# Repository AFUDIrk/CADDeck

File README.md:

# CADdeck

The english [Manual](/READMEeng.md) 

Hierbei handelt es sich um ein kombiniertes Joystick- und Touchpanel-Display, das für die Verwendung mit gängigen CAD-Programmen geeignet ist. Es beinhaltet:
1. Zwei-Achsen-Joystick (z. B. für X-, Y-Schwenk)
2. Hall-Sensoren im Joystick-Griff (z. B. für Zoom und Drehung) mit einem berührungslosen Sensor (z. B. zum Bewegen der Komponente in Kombination mit dem Joystick)
3. Zehn Schalter rund um die Basis (z. B. Messen, ESC...)
4. LCD-Touchpanel mit bis zu 10 Bildschirmen und 12 Tasten

Alle H/W-Tasten und die Touchpanel-Tasten sind über eine Website programmierbar.

Die Verbindung zum PC erfolgt per Bluetooth über die HID-Schnittstelle (d. h. für den PC sieht es aus wie eine Tastatur und eine Maus).
Für die Stromversorgung und das Herunterladen von Code steht ein USB-C-Anschluss zur Verfügung.
Der USB-C-Anschluss auf der Rückseite dient der Stromversorgung zum Hochladen des Codes.
Es sollte möglich sein, das Gerät mit Strom zu versorgen und es fest mit dem Bildschirm zu verbinden, anstatt es über USB-C mit Strom zu versorgen, aber das habe ich noch nicht versucht.

Es wurde von Andrew eine USB-Schnitstelle mit einem RP2040 hinzugefügt, mit der das CADDeck 6DOF fähig ist. Es wird noch daran gearbeitet, den Code so zu ändern,
das nur noch ein Prozessor gebraucht wird. Momentan ist noch eine Bluetooth- und eine USB-Verbindung nötig, damit das ganze funktioniert.

Die Firmware für den RP2040 ist von https://github.com/jfedor2/magellan-spacemouse.
Die Version für das CADDeck ist hier zu finden: https://github.com/AFUDIrk/magellan-spacemouse

## Touch-Panel
Das Touchpanel ist von Dustin Watts FreeTouchDeck-Projekt (https://github.com/DustinWatts/FreeTouchDeck.git) inspiriert, das ich modifiziert habe, um die Anzahl der Tasten zu erhöhen.
usw. (https://github.com/andrewfernie/FreeTouchDeckWT32.git). Für dieses Projekt habe ich Joystick-, Hallsensor- und Tastenunterstützung hinzugefügt.
Der einfachste Weg, dies in Gang zu bringen, ist die Verwendung einer WT32-SC01-Karte (http://www.wireless-tag.com/portfolio/wt32-sc01/).
Kaufen Sie das Basisboard, nicht die „Plus“-Version, da das Plus eine parallele Schnittstelle zum LCD-Panel nutzt und nicht genügend IO-Leitungen für den Joystick und die Tasten frei lässt.
usw. Das Board enthält ein ESP32-Modul und ein 3,5-Zoll-LCD mit kapazitivem Touchscreen.

## S/W-Aufbau-Hinweise:
1. Der Build verwendet die PlatformIO-IDE für VSCode. Installieren Sie VSCode, dann das PlatformIO-Plugin und schon kann es losgehen.
2. Sie müssen sicherstellen, dass die entsprechenden Pins für Ihre Hardwarekonfiguration definiert sind. Ich habe meines für den WT32-SC01 gebaut und den Code für ein handverdrahtetes ESP32-Modul + einen resistiven Touchscreen erstellt.
3. Möglicherweise sehen Sie Build-Meldungen wie
 
In der Datei, die aus include/CADDeck.h:14 enthalten ist,
aus include/SaveConfig.h:3,
von src/SaveConfig.cpp:1:
.pio/libdeps/esp-wrover-kit/TFT_eSPI/TFT_eSPI.h:909:8: Warnung: #warning >>>>------>> TOUCH_CS-Pin nicht definiert, TFT_eSPI-Touchfunktionen sind nicht zugänglich! [-Wcpp]
#Warnung >>>>------>> TOUCH_CS-Pin nicht definiert, TFT_eSPI-Touchfunktionen sind nicht verfügbar!`
 
Sie können diese beseitigen, indem Sie TOUCH_CS in platformio.ini für jeden nicht verwendeten Pin definieren, der ein gültiger Ausgabepin ist.
Die Alternative besteht darin, TOUCH_CS nicht zu definieren (die Zeile löschen oder ein Semikolon davor einfügen) und die Meldungen einfach zu ignorieren.

#define TOUCH_CS=33

4. Das System versucht beim Start, das Logo in CADDeck_logo.bmp anzuzeigen. Wenn Sie nicht möchten, dass etwas angezeigt wird, stellen Sie sicher, dass die Datei nicht existiert. In diesem Fall wird auf der seriellen Schnittstelle eine Meldung wie die folgende angezeigt.
Solange Sie beim Start nichts gesehen haben, ignorieren Sie die Meldung.
 
[ 1159][E][vfs_api.cpp:104] open(): /littlefs/logos/CADDeck_logo.bmp existiert nicht, keine Berechtigungen zum Erstellen

5. Möglicherweise werden Ihnen Fehlermeldungen wie z. B. angezeigt
 
[vfs_api.cpp:104] open(): /littlefs/list existiert nicht
 
Dies ist ein bekanntes Problem mit ESPAsyncWebsServer im Zusammenhang mit von LittleFS unterstützten Ordnern, während dies bei SPIFFS nicht der Fall ist. Siehe https://github.com/lorol/

6. Haben Sie Probleme? Es gibt einige Debug-Meldungen, die in FreeTouchDeck.h aktiviert werden können
 
#define LOG_MSG_BASIC 1
#define LOG_MSG_LEVEL 1 // 1=FEHLER, 2=FEHLER+WARN, 3=FEHLER+WARN+INFO
#define LOG_MSG_DEBUG 0
#define LOG_MSG_TOUCH_DEBUG 0 // Meldungen an die Konsole jedes Mal, wenn eine Berührung erkannt wird

Versuchen Sie, LOG_MSG_LEVEL auf 3 zu setzen, und Sie erhalten weitere Statusmeldungen

# Hardware-Aufbau

Der größte Teil der Montage ist einfach und besteht größtenteils aus der Verkabelung.
Vollständige 3D-CAD-Modelle werden sowohl im Fusion360- als auch im STEP-Format im Ordner „hardware/model“ bereitgestellt.

Die Verweise auf Tastennummern werden in diesem Diagramm angezeigt:

## Gehäuse
Ein Fusion360-Modell des Falls und STL-Dateien sind im CADDeck-Repository enthalten. Das Hauptgehäuse ist zweiteilig bedruckt.
Das Ober- und Unterteil wird von unten mit M3-Kopfschrauben verschraubt.

Es gibt keine offensichtliche Möglichkeit, den Bildschirm am Gehäuse zu befestigen. Deshalb habe ich das Gehäuse so entworfen, dass es das Display mit einem Rahmen hält.
Zuerst wird das Display in das Gehäuse geschoben, bis es in den hinteren Abstandshaltern einrastet.
Anschließend wird die TPU-Dichtung zwischen Gehäuse und Display geschoben und abschließend die beiden vorderen Abstandshalter eingefügt.
Bei Bedarf kann das Display mit zwei Schrauben von hinten gegen die TPU-Dichtung gedrückt werden.
Aber war bei mir nicht nötig.

Die USB-C-Adapterplatine wird mit zwei selbstschneidenden Schrauben an der kleinen Basis befestigt.

6 x M3-Flachkopfschrauben gehen durch die Unterseite des Gehäuses und dienen dazu, das Gehäuse geschlossen zu halten.
4 x M3-Flachkopfschrauben kommen durch die Unterseite des Gehäuses und dienen zur Befestigung sowohl des Joysticks als auch der Schalterplatte mit den 10 Schaltern.

## Joystick-Knopf

Der knifflige Teil ist die Joystick-Taste und insbesondere die Magnete und Hall-Sensoren. Der obere Hallsensor wird direkt eingeklebt
und das untere habe ich vorher auf eine kleine Lochmusterplatine gelötet und dann mit Sekundenkleber befestigt.
Für die Erstellung steht auch ein Platinenlayout zur Verfügung.
Platinen für die 10 Schalter und für den Taster habe ich bereits anfertigen lassen, dadurch ist der Aufbau übersichtlicher und die Verkabelung der MX-Taster entfällt.

Der Joystick-Knopf besteht aus mehreren 3D-gedruckten Teilen.
Im Inneren des Joystick-Knopfes befinden sich mehrere Magnete, die sich gegenseitig abstoßen und ihn so in einer schwebenden Position halten. Ich habe etwas Sekundenkleber verwendet
um die Magnete anzubringen. Sie können einfach einen Tropfen Sekundenkleber durch das kleine Loch im Kunststoff tropfen lassen.
Im Bildverzeichnis finden Sie eine Darstellung der Anordnung der Magnete (N+S).

Wenn alle Magnete montiert sind, werden das Kreuz und der Magnethalter vorsichtig zusammengesteckt und dann gedreht, sodass die Magnete übereinander liegen.
Anschließend werden die drei Führungsstifte mit etwas Fett eingesetzt, sie halten die beiden Teile zusammen.
Ein M4x16mm Abstandshalter aus Messing wird von oben in die Grundplatte eingedrückt (ggf. mit etwas Kleber fixieren).
Anschließend die Grundplatte mit etwas Fett von unten in das Kreuz einsetzen und auf Leichtgängigkeit achten.
Abhängig davon, wie genau Ihr Drucker druckt, muss die Achse möglicherweise bearbeitet werden.
Ich habe eine M4-Schraube in die Grundplatte geschraubt, diese in einen Akkuschrauber eingespannt und abgeschliffen, bis sie passte.
Die Bodenplatte mit den Magneten wird mit drei selbstschneidenden Schrauben befestigt.
Der Touchsensor wird mit Kleber am Deckel befestigt, der Deckel wird ganz am Ende in das Rad geschoben und sollte ohne Kleber halten.

Die Drähte vom Berührungssensor und vom oberen Hallsensor werden durch Löcher nach unten geführt.
Bitte lassen Sie die Kabel etwas länger, da der Joystick-Knopf später auf den Joystick aufgedreht wird.

Alle 10 MX-Taster werden am Schaltpult genutzt und entsprechend dem Schaltplan verdrahtet.
Der PCF8575 wird mit selbstschneidenden Schrauben an der Adapterplatte befestigt.
Zuerst den Joystick von unten einsetzen, dann die Adapterplatte und dann die Schalterkonsole.
Setzen Sie den Schaumstoff von oben ein, drehen Sie dann den Joystick-Knopf auf den Joystick und verlegen Sie die Kabel nach unten unter den Schaumstoff.
Der Joystick-Knopf wird am Joystick befestigt und von oben mit einer M4-Stiftschraube gekontert, sodass er fest auf der Joystick-Achse sitzt.
Jetzt ist das Gehäuse zusammengebaut. Schrauben Sie zunächst alle Schrauben von unten locker ein. Ziehen Sie dann die sechs äußeren Schrauben fest.
Richten Sie nun die Schalterkonsole so aus, dass die Schalterkappen nicht verklemmen und ziehen Sie abschließend die letzten vier Schrauben fest.

Im Bilderverzeichnis gibt es noch ein paar Bilder, wie ich die Stütze ausgedruckt habe.

## Verkabelung
Ein [Schaltplan](hardware/Electrical/WiringDiagram10Buttons.pdf) ist im Ordner hardware/electrical enthalten. Das meiste davon ist unkompliziert.

## Teileliste
Menge  1 [ESP32-SC01 LCD-Touchscreen] (https://www.aliexpress.com/item/1005004399769442.html)

Menge  1 [2mm 2x20 Pin Header](https://www.aliexpress.com/item/1005001852671581.html)

Menge  1 [Kapazitiver Berührungsschalter TTP223](https://www.aliexpress.com/i/33012282190.html)

Menge 10 [Cherry MX Button](https://www.ebay.de/itm/183967039197) (Diese gibt es in verschiedenen Ausführungen. Mit oder ohne Klick, starker oder leichter Widerstand.)

Menge  1 [FrSky M9 Joystick] (https://www.ebay.de/itm/374032459911) Dieses Gerät ist etwas teuer, aber von guter Qualität.
         Funktionell gibt es nichts Besonderes – man braucht nur etwas mit analogen X- und Y-Ausgängen.

Menge  1 [PCF8575 I2C IO Expander] (https://www.aliexpress.com/item/1005004433286881.html)

Menge  1 [USB-C-Adapterplatine] (https://www.aliexpress.com/item/1005003446036071.html)

Menge  2 [Hallsensoren 49E](https://www.aliexpress.com/item/1903819684.html)

Menge 40 [Klebe-Ausgleichsgewichte](https://www.ebay.de/itm/363221786745) (Bei Bedarf. Als ich den Knopf hochzog, war das Gehäuse zu leicht für mich.
         Sie können aber auch etwas anderes verwenden, um das Gewicht zu erhöhen.)

Menge 10 10k 1/8W Push-Through-Widerstände Cherry MX-Druckknopf

Menge  6 M3-Messingeinsätze (für Gehäuseoberseite)

Menge  3 M2-Messingeinsätze (für den Joystick-Knopf zum Befestigen des Rads)

Menge  3 selbstschneidende Schrauben 2,2x5mm (für Magnethalter unten)

Menge 11 Neodym-Magnete N52 5x5x1mm (9 Stück für die Drehbewegung und zwei Stück übereinander für den Hallsensor)

Menge  6 Neodym-Magnet N52 8x1mm (in der Joystick-Taste oben und unten)

Menge  3 Neodym-Magnet N52 8x3mm (im Joystick-Knopf in der Mitte)

Menge  6 Schrauben M3x10mm (für das Gehäuse)

Menge  4 Schrauben M3x20mm (zur Befestigung des Joysticks)

Menge  9 Schrauben M2x5mm (zur Befestigung des Rads an der Joystick-Taste, der USB-C-Platine und zur Befestigung des PCF8575)

Menge  1 M4x16mm Sechskant-Abstandsbolzen 

Menge  1 JST RM 2,54 mm Stecker und Stiftleiste  5-polig

Menge  1 JST RM 2,54 mm Stecker und Stiftleiste  4-polig

Menge  1 JST RM 2,54 mm Stecker und Stiftleiste 10-polig

Leicht weicher Schaumstoff (zwischen Joystick-Taste und Joystick)

26 AWG (0,14 mm²) Silikondraht für die Verbindung zwischen den Platinen(vorzugsweise in mehreren Farben, um Verwechslungen zu vermeiden)

30 AWG (0,05 mm²) Silikondraht für den Knopf(vorzugsweise in mehreren Farben, um Verwechslungen zu vermeiden)

# Aufstellen
Sobald das Gerät zusammengebaut ist und das Display erscheint, sollten Sie die Hauptseite sehen.

Gehen Sie zur Seite CAD-Einstellungen.

Dann die Seite Switch Monitor.

Es zeigt den Status des Joysticks, des Push-Sensors und der Tasten an. Sie sollten das Ergebnis jeder Joystick-Bewegung oder Tastenauswahl sehen können.
Beachten Sie, dass die Werte als 1 angezeigt werden, wenn sie nicht ausgewählt sind, und als 0, wenn sie ausgewählt (gedrückt) sind.

Die X- und Y-Daten des Joysticks sowie die Dreh- und Zoomdaten können leicht schwanken. Das ist normal, da der Joystick zu diesem Zeitpunkt noch nicht kalibriert ist.
So kalibrieren Sie den Joystick und den Knopf:
1. Gehen Sie zurück zur Seite CAD-Einstellungen
2. Drücken Sie die Joystick-Nulltaste, wenn der Joystick zentriert und stationär ist. Dadurch wird der Nullpunkt für Joystick und Knopf festgelegt.
3. Drücken Sie die Joystick-Skalentaste und bewegen Sie den Joystick zum äußersten X- und Y-Punkt, drehen Sie den Knopf und drücken Sie ihn nach oben und unten.
   Du hast 5 Sekunden Zeit.
   Sobald die Funktion abgeschlossen ist, werden die Kalibrierungsparameter berechnet und alle Achsen sollten einen Bereich von ungefähr +/- 1 sowohl in X als auch in Y anzeigen.
4. Wenn Sie mit der Kalibrierung zufrieden sind, klicken Sie auf die Schaltfläche „CAD-Konfiguration speichern“ und die Parameter werden in der Datei cadparams.json im ESP32 gespeichert.
   Diese Datei kann vom ESP32 über die Seite CAD-Einstellungen im Konfigurator auf Ihren PC heruntergeladen werden.
   Es empfiehlt sich, dies zu tun und die Datei in den Ordner data\config im CADDeck-Code zu kopieren, damit Sie die Parameter nicht verlieren, wenn Sie den Datenordner das nächste Mal auf den ESP32 hochladen.
4. Wenn Sie mit den Ergebnissen nicht zufrieden sind, versuchen Sie es erneut.

Verbinden Sie Ihren Computer über die Bluetooth-Einstellungsseite Ihres Computers mit CADDeck.

# Konstruktion
Bitte beachten Sie, dass es sich bei allen oben gezeigten oder erwähnten Seiten um Beispiele handelt. Jede Seite kann über den Konfigurator neu organisiert und an Ihre Bedürfnisse angepasst werden.

## WLAN-Konfiguration
Der Zugriff auf den Konfigurator erfolgt über einen Webbrowser auf einem Computer oder Tablet, der mit demselben Netzwerk wie der ESP32 verbunden ist.
Um den Konfigurator zu aktivieren, gehen Sie auf die Einstellungsseite des Touchpanels und wählen Sie die Schaltfläche „WLAN aktivieren“.

Wenn Sie Ihre WLAN-Verbindung bereits in wificonfig.json konfiguriert haben, sollte eine Meldung angezeigt werden, dass das WLAN verbunden ist und die IP-Adresse angezeigt wird.
An dieser Stelle können Sie zu Ihrem Browser gehen und die IP-Adresse von top connect eingeben. Der Konfigurator wird angezeigt.

Wenn Sie das WLAN noch nicht konfiguriert haben, sollte eine Meldung angezeigt werden, dass ein Zugangspunkt (AP) mit einem Netzwerknamen und einer IP-Adresse erstellt wurde.
Sie müssen Ihren Computer mit dem bereitgestellten Netzwerk verbinden und dann Ihren Browser auf die IP-Adresse verweisen.
Sobald der Konfiguratorbildschirm in Ihrem Browser erscheint, gehen Sie zur WLAN-Seite und geben Sie Ihre Netzwerk-SSID und Ihr Passwort ein. Wählen Sie dann „Save WiFi Config“, um die Einstellungen zu speichern.

## Menükonfiguration
Die wichtigste Änderung gegenüber dem ursprünglichen FreeTouchDeck besteht darin, dass mehr Tasten pro Seite möglich sind – die Bildschirmfläche ist nur geringfügig kleiner als die Größe von zwölf StreamDeck-Tasten, was vernünftig erscheint.
Der Code ist derzeit auf drei Reihen mit je vier Schaltflächen eingestellt, kann jedoch durch Ändern von CADDeck.h in drei Reihen mit je fünf Schaltflächen (oder zwei Reihen mit je vier Schaltflächen usw.) geändert werden: „#define BUTTON_ROWS 3“ und „#define BUTTON_COLS 5“. „. ".
Grundsätzlich sollte es größere Arrays unterstützen, wurde aber nicht getestet und die Konfiguratorseite ist auf maximal 3x5 eingestellt.

Der Konfigurator zeigt eine Reihe von drei Reihen mit fünf Schaltflächen an, mit einer Dropdown-Liste zur Auswahl der zu ändernden Menüseite.
Wenn Sie weniger als 3x5 verwenden, ignorieren Sie einfach die zusätzlichen Zeilen und Spalten. Auf der To-Do-Liste steht die dynamische Generierung des HTML-Codes, um ihn an die Anzahl der Zeilen und Spalten anzupassen.

Jede Menüseite verfügt über eine 2D-Reihe programmierbarer Tasten und jede Taste verfügt über eine Reihe von 3 Aktionen, die beim Drücken der Taste definiert werden können.

Sie können unterschiedliche Hintergrundfarben für eine Schaltfläche festlegen, die eine Aktion ausführt (schwarzer Hintergrund im Bild oben) oder für Links zu einem anderen Menü (hellblau im Bild).
Dies wird auf der Seite „Einstellungen“ des Konfigurators gesteuert.

Wenn Sie nicht alle Buttons nutzen möchten, stellen Sie im Konfigurator das Logo auf „blank.bmp“ ein und achten Sie darauf, dass für diesen Button keine Aktionen definiert sind.
Schaltflächen mit diesen Eigenschaften werden nicht gezeichnet.

Eine Einschränkung ist die Größe des FLASH, der für die auf dem Touchscreen angezeigten Konfigurationsdateien und Symbole verwendet wird. Bei den Symbolen handelt es sich um 75x75 24-Bit-Farb-BMP-Dateien.
Jeder benötigt etwa 17 KB. Wenn Ihnen der Speicherplatz ausgeht, besteht Ihre einzige Möglichkeit darin, zu prüfen, ob noch freier Speicherplatz vorhanden ist, und ihn zu löschen.

## Hardwareschlüssel
Die Hardwaretasten werden über eine spezielle Seite innerhalb desselben webbasierten Konfigurators wie für das LCD-Panel konfiguriert.

Der obere Abschnitt umfasst:
1. Aktuelles CAD-Programm: Dies ist das Programm, dessen Einstellungen geladen werden, wenn CADDeck neu gestartet wird
2. X- und Y-Skalierungsparameter für Joystick und Knopf. Diese können manuell eingestellt werden
   Es gibt jedoch eine Funktion, die Daten sammelt, während der Joystick ganz nach unten gedrückt wird, und den Maßstab für Sie berechnet. Die Ausgabeskalierung beträgt +/-1
3. Deadzone von Joystick und Knopf. Jeder X- oder Y-Wert mit einem absoluten Wert unter dieser Zahl wird auf Null gesetzt.
4. Joystick-Empfindlichkeit. Joystick-Werte werden bei der Umwandlung in Mausbewegungsbefehle damit multipliziert
5. Empfindlichkeit des Knopfes. Der Knob-Wert wird damit multipliziert und in Mausbewegungsbefehle umgewandelt
6. Steady Time: Nachdem der Joystick länger als diese Zeitspanne zentriert war, ohne dass eine Schwenk- oder Drehtaste ausgewählt wurde, kehrt der Joystick in seinen Standardmodus (normalerweise Mauszeiger) zurück.

Darunter befindet sich die Definition der Tastenaktion. Zur Definition der Aktionen wird derselbe Ansatz wie für die Tasten auf dem LCD-Panel verwendet. Die Aktionen sind:
1. Ausgewähltes CAD-Programm. Das Programm, dessen Einstellungen in diesem Teil des Konfigurators geändert werden. Für jedes der fünf verfügbaren CAD-Programme werden separate Definitionen dieser Einstellungen gepflegt.
2. Ausgewählte Schaltfläche. Eine der neun im Bild links gezeigten Schaltflächen. Klicken Sie auf einen der angegebenen Bereiche im Bild und ändern Sie dann die Aktionen für diese Schaltfläche nach Bedarf.
3. Die Aktionen, die ausgeführt werden müssen, damit der Joystick (z. B. die Maus) das Schwenken/Drehen/Zoomen im ausgewählten CAD-Programm steuern kann.
Beachten Sie, dass die Definition dessen, was zum Steuern von Schwenken/Drehen/Zoomen erforderlich ist, unabhängig davon ist, welche Taste diesen Modus aktiviert.
Beispielsweise muss bei Solidworks die mittlere Maustaste gedrückt gehalten werden, um die Ansicht zu drehen. Daher ist „JoystickRotate/Action1“ auf „Maustasten“ und „Value1“ auf „Drücken Sie die mittlere Taste“ eingestellt.
Um die Funktion „Drehen“ der Schaltfläche 8 zuzuweisen, klicken Sie im Bild links auf 8 und setzen Sie dann „SelectedButton/Action1“ auf „CAD Functions“ und „Value1“ auf „Joystick Rotate“.

Unten befindet sich die Schaltfläche „CAD-Konfiguration speichern“. Bei Auswahl werden die Einstellungen für alle CAD-Programme auf dem ESP32 in der Datei caparams.json gespeichert

## Standardkonfiguration
Während über den Konfigurator alles geändert werden kann, gibt es einige Standardeinstellungen, die mit dem Code bereitgestellt werden.
Diese sind:

### Kontrollzuweisungen
1. Joystick bewegt die Komponente
2. Joystick mit gedrücktem Drucksensor (0), bewegt das Bauteil
3. Durch Drehen des Joystick-Knopfes wird die Ansicht gedreht
4. Durch Drücken oder Ziehen der Joystick-Taste wird vergrößert bzw. verkleinert
5. Schaltfläche 1 ist die Modellsymbolleiste („S“ in Fusion360).
6. Schaltfläche 2 ist Filet („F“ in Fusion360)
7. Taste 3 ist Push Pull („Q“ in Fusion360)
8. Schaltfläche 4 ist Extrudieren („E“ in Fusion360)
9. Mit Taste 5 wird die Auswahl aufgehoben („ESC“ in Fusion360 und Solidworks).
10. Schaltfläche 6 ist Linie („L“ in Fusion360)
11. Schaltfläche 7 ist ein Rechteck mit zwei Punkten („R“ in Fusion360)
12. Schaltfläche 8 ist Spline (ich habe es in Fusion360 auf „W“ gesetzt)
13. Schaltfläche 9 ist ein Kreis („C“ in Fusion360)
14. Schaltfläche 10 ist Zeile („Zurück“ in Fusion360)

### Menüs
Menünummern werden wie folgt vergeben:
1. Menü 0: Hauptmenü
2. Menü 1: Systemeinstellungen
3. Menü 2: CAD-Einstellungen
4. Menü 3: Nicht verwendet
5. Menü 4: Nicht verwendet
6. Menü 5: Nicht verwendet
7. Menü 6: Nicht verwendet
8. Menü 7: Aktives CAD-Programm auswählen
9. Menü 8: Fusion360-Aktionen
10. Menü 9: Nicht verwendet
 
Wenn Sie Unterstützung bei der Einrichtung oder beim Beschaffen der Platinen benötigen,
können Sie meinem Discord-Server beitreten.https://discord.gg/kFvPhqmc

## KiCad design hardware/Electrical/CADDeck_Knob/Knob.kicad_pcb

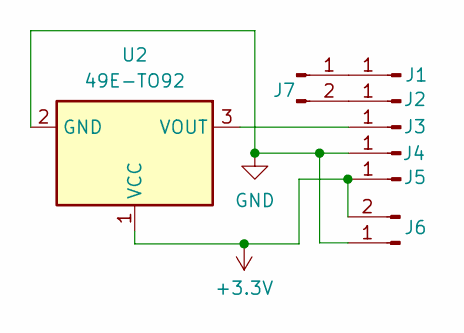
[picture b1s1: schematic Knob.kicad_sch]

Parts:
J1, J2, J3, J4, J5: Conn_01x01_Pin; Pin_D2.0mm_L3.0mm_FlatFork
J6, J7: Conn_01x02_Pin; PinHeader_1x02_P2.54mm_Vertical
U2: 49E-TO92

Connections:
+3.3V: J5.1, J6.2, U2.1 (VCC)
GND: J4.1, J6.1, U2.2 (GND)
unnamed: J1.1, J7.1
unnamed: J2.1, J7.2
unnamed: J3.1, U2.3 (VOUT)

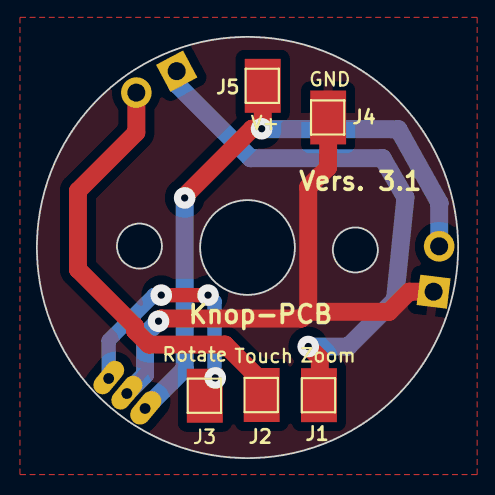
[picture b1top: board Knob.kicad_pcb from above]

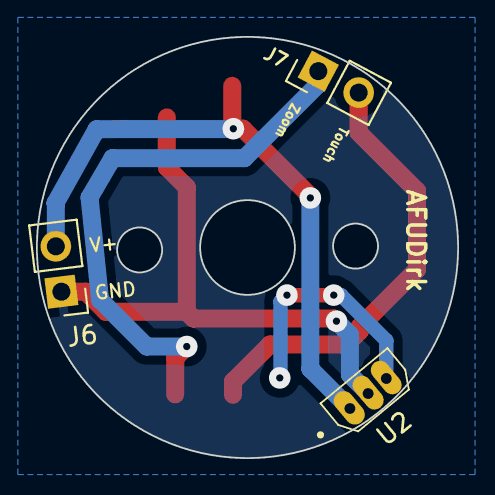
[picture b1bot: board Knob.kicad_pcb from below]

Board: 2 copper layers, 23.4 x 23.4 mm, 8 parts (3 on the bottom side), 5 nets.

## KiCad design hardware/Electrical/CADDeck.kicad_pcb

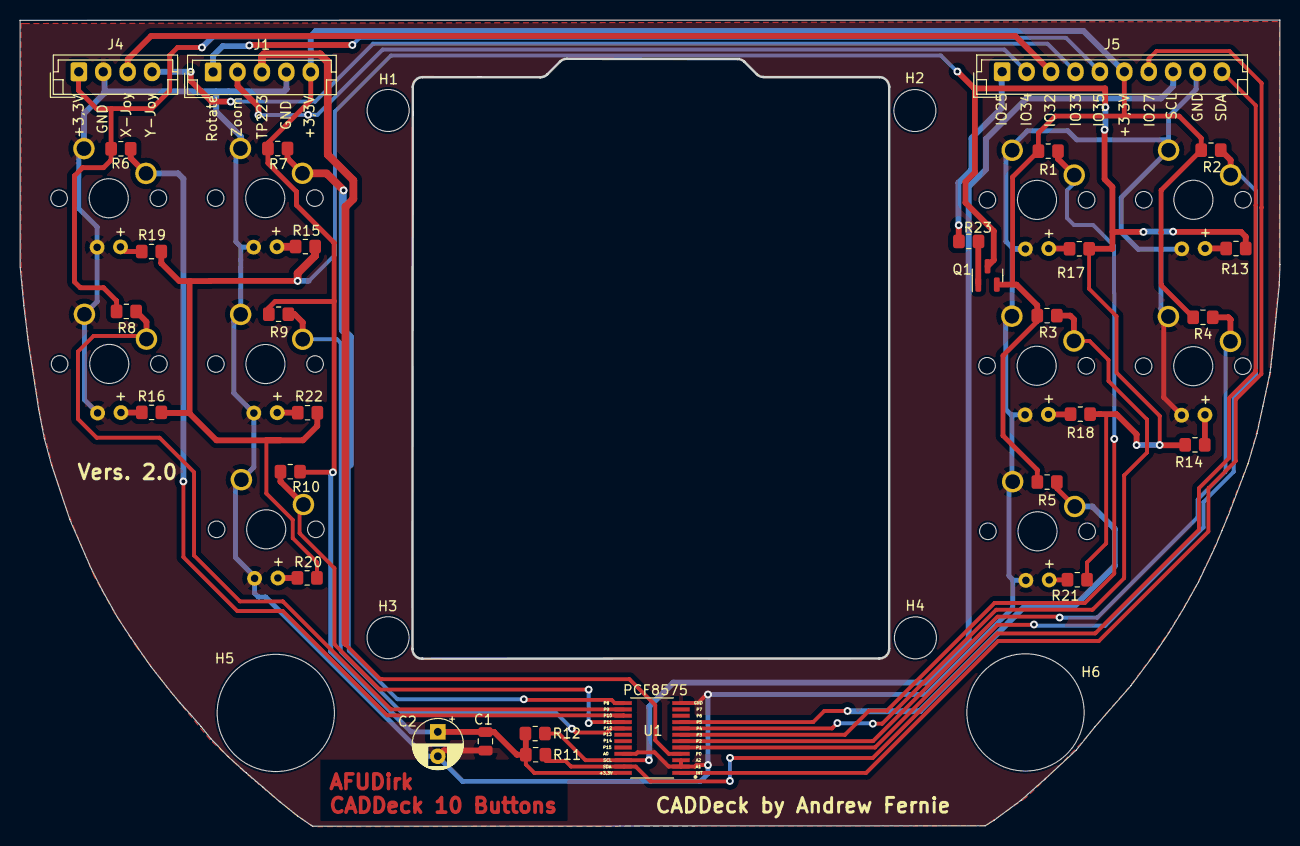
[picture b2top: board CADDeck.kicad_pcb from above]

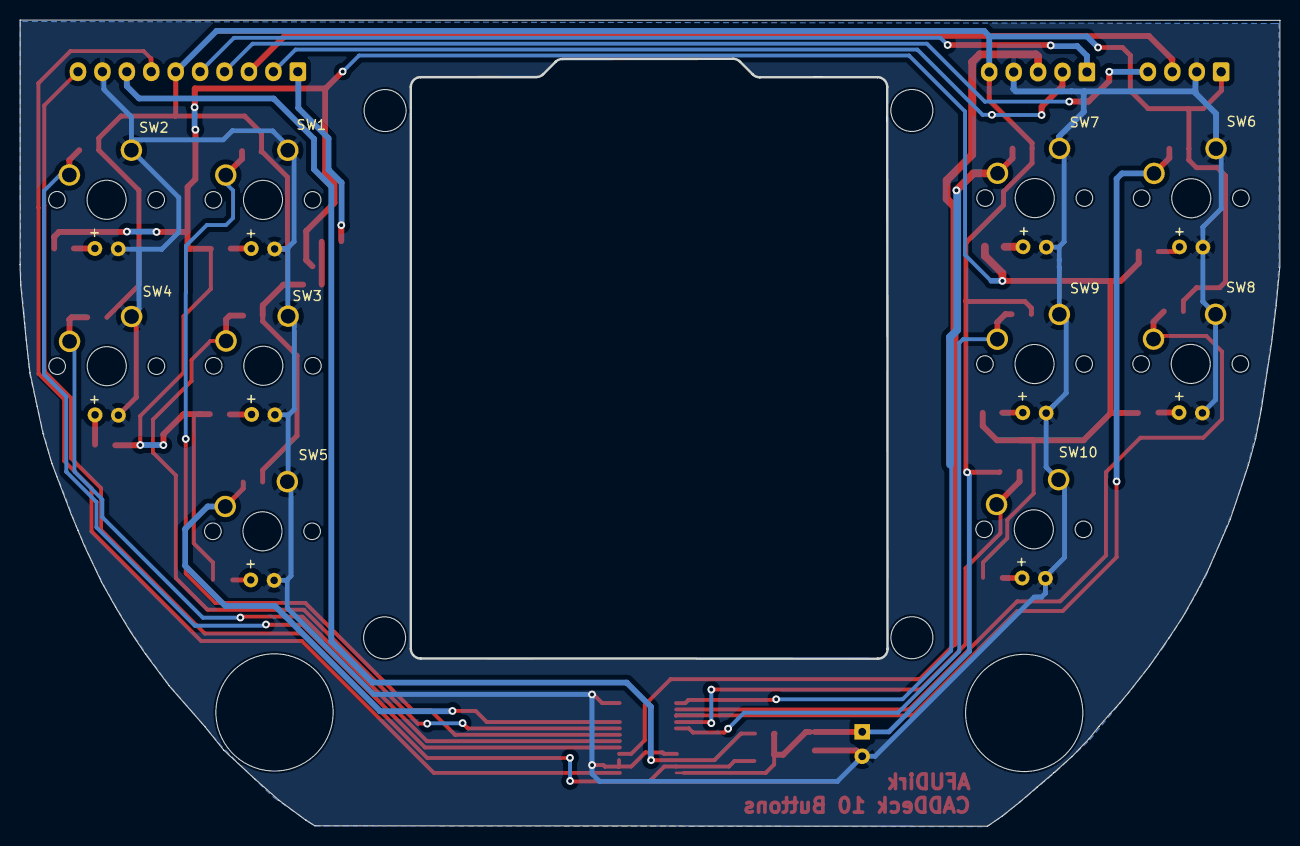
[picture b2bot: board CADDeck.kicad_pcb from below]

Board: 2 copper layers, 129.0 x 82.5 mm, 46 parts (10 on the bottom side), 33 nets.

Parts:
C1: 100nF; C_0805_2012Metric
C2: 10uF/6V; CP_Radial_D5.0mm_P2.50mm
H1, H2, H3, H4: MountingHole 4mm; MountingHole_4.3mm_M4
H5, H6: MountingHole 12mm; MountingHole_8.4mm_M8
J1: Conn_01x05_Socket; JST_EH_B5B-EH-A_1x05_P2.50mm_Vertical
J4: Conn_01x04_Socket; JST_EH_B4B-EH-A_1x04_P2.50mm_Vertical
J5: Conn_01x10_Socket; JST_EH_B10B-EH-A_1x10_P2.50mm_Vertical
Q1: 2N2222; SOT-23
R1, R2, R3, R4, R5, R6, R7, R8, R9, R10, R11, R12: 10k; R_0805_2012Metric_Pad1.20x1.40mm_HandSolder
R13, R14, R15, R16, R17, R18, R19, R20, R21, R22: 100; R_0805_2012Metric_Pad1.20x1.40mm_HandSolder
R23: 1k; R_0805_2012Metric_Pad1.20x1.40mm_HandSolder
SW1, SW2, SW3, SW4, SW5, SW6, SW7, SW8, SW9, SW10: SW_Push; Cherry_MX_LED
U1: PCF8575PWE4; SOP65P640X120-24N

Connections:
+3.3V: C1.2, C2.1, J1.5, J4.1, J5.6, Q1.2 (E), R1.1, R2.1, R3.1, R4.1, R5.1, R6.1, R7.1, R8.1, R9.1, R10.1, R11.1, R12.1, U1.24 (VCC)
GND: C1.1, C2.2, J1.4, J4.2, J5.9, SW1.1, SW1.3 (Kathode_-), SW2.1, SW2.3 (Kathode_-), SW3.1, SW3.3 (Kathode_-), SW4.1, SW4.3 (Kathode_-), SW5.1, SW5.3 (Kathode_-), SW6.1, SW6.3 (Kathode_-), SW7.1, SW7.3 (Kathode_-), SW8.1, SW8.3 (Kathode_-), SW9.1, SW9.3 (Kathode_-), SW10.1, SW10.3 (Kathode_-), U1.2 (A1), U1.3 (A2), U1.12 (GND), U1.21 (A0)
unnamed: J1.1, J5.5
unnamed: J1.2, J5.2
unnamed: J1.3, U1.4 (P00)
unnamed: J4.3, J5.3
unnamed: J4.4, J5.4
unnamed: J5.1, R23.1
unnamed: J5.7, U1.1 (~INT)
unnamed: J5.8, R12.2, U1.22 (SCL)
unnamed: J5.10, R11.2, U1.23 (SDA)
unnamed: Q1.1 (B), R23.2
unnamed: Q1.3 (C), R13.2, R14.2, R15.2, R16.2, R17.2, R18.2, R19.2, R20.2, R21.2, R22.2
unnamed: R17.1, SW1.4 (Anode_+)
unnamed: R13.1, SW2.4 (Anode_+)
unnamed: R18.1, SW3.4 (Anode_+)
unnamed: R14.1, SW4.4 (Anode_+)
unnamed: R21.1, SW5.4 (Anode_+)
unnamed: R19.1, SW6.4 (Anode_+)
unnamed: R15.1, SW7.4 (Anode_+)
unnamed: R16.1, SW8.4 (Anode_+)
unnamed: R22.1, SW9.4 (Anode_+)
unnamed: R20.1, SW10.4 (Anode_+)
unnamed: R2.2, SW2.2, U1.5 (P01)
unnamed: R4.2, SW4.2, U1.6 (P02)
unnamed: R1.2, SW1.2, U1.7 (P03)
unnamed: R3.2, SW3.2, U1.8 (P04)
unnamed: R5.2, SW5.2, U1.9 (P05)
unnamed: R7.2, SW7.2, U1.13 (P10)
unnamed: R8.2, SW8.2, U1.14 (P11)
unnamed: R6.2, SW6.2, U1.15 (P12)
unnamed: R10.2, SW10.2, U1.16 (P13)
unnamed: R9.2, SW9.2, U1.17 (P14)

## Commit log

2023-03-14 Create AFUDirk Case
    Ein von mir erstelltes Gehäuse für das CADDeck.
    Ist noch in Beabeitung!!!!
2023-03-16 Create CADDeck Case AFUDirk.f3d
    Mein Gehäuse
2023-03-16 Update CADDeck Case AFUDirk.f3d
    Es sind immer noch Änderungen möglich
2023-03-16 Create CADDeck Case AFUDirk.f3d
    In neues Verzeichniss verschoben
2023-03-16 Delete CADDeck Case AFUDirk.f3d
    In anderes Verzeichniss verschoben
2023-03-16 Update CADDeck Case AFUDirk.f3d
    Ein paar Korrekturen
2023-03-16 Druckdateien
    Druckdateien hinzugefügt
2023-03-17 Update CADDeck Case AFUDirk.f3d
    Habe das Lager entfernt
2023-03-17 Fertig gestellt
    Fertig gestellt
2023-03-17 Bilder
2023-03-17 Fertig zum Drucken
2023-03-17 Hatte noch einen Fehler
    die Tiefe vom Magnet geändert
2023-03-17 Hatte Radius vergessen
2023-03-17 Fertig
2023-03-18 Steckerhalter hinzugefügt
2023-03-21 Nur ein paar Verfeinerungen
2023-03-22 Magnet Tiefe geändert
2023-03-23 Update Joystick.f3d
    Tolleranz verkleinert
2023-03-23 Schrauben und Stückliste
    hinzugefügt
2023-03-23 Printfiles hinzugefügt
2023-03-23 Gewindeeinsätze hinzugefügt
2023-03-23 Bohrung im Würfel verkleinert
2023-03-23 Würfel Bohrung geändert durchgehend
2023-03-23 Achse Würfel
    Zentrierbohrung angebracht
2023-03-24 Achsen geändert
    Flächen angebracht dien das mitdrehen verhindern
2023-03-24 Magnetjustage
    Es mussten einige Teile geändert werden, da ich andere Magnete und deren Position verändert habe. Muss erst noch testen, ob es jetzt funktioniert.
2023-03-24 Magnetplatte verstärkt
2023-03-24 Bohrungen an den Achsen geändert
2023-03-25 Magnetabstand geändert
2023-03-25 Würfelbohrung und Achse geändert
2023-03-25 Magnete Bohrungen vergrößert
2023-03-25 kleine Änderung
2023-03-26 Fast fertig
2023-03-26 Magnetposition verändert
2023-03-29 Grundplatte
    Magnetposition verändert, damit das Rad besser zentriert wird.
2023-03-31 kleine Maßänderungen
    optimiert
2023-04-01 Aufnahme Hallsensoren verstärkt
2023-04-01 kleine Optimierung
2023-04-02 Schaltplan geändert
2023-04-02 Magnetposition geändert
2023-04-03 Update Platte.3mf
    Magnetanordnung geändert.
2023-04-04 Delete Platte.3mf
    Der untere Hallsensor muss noch getestet werden.
2023-04-05 Magnet Rotate neu angeordnet
    Platine in der Grundplatte verbessert die elektrische Verbindungsstabilität.
2023-04-05 Bilder hinzugefügt
2023-04-14 Software geändert
    Option für 10 Buttons hinzugefügt.
2023-04-14 Update DrawHelper.cpp
    Hatte eine Taste vergessen
2023-04-17 Kleine Veränderungen
    und Bild aktualisiert
2023-04-17 Update index.htm
    Versuch mit 10 Tasten
2023-04-17 Update index.htm
    Teils ins deutsche übersetzt, aber noch nicht vollständig
2023-04-17 Update index.htm
    Noch ein bisschen ins deutsche übersetzt, aber noch nicht vollständig
2023-04-17 Übersetzung
    Noch ein paar Zeilen ins deutsche übersetzt
2023-04-17 Update ConfigHelper.cpp
    Übersetzung in Deutsch
2023-04-18 Alles Komplett hochgeladen
    Alles Komplett hochgeladen mit Übersetzung in Deutsch
2023-04-20 Gewinde war gerissen
    Langmutter zur Verstärkung integriert
2023-04-21 Modell fertig gestellt
    Alle Teile passen mechanisch zusammen.
    Am Gehäuse Oberteil habe ich nur die Bohrung für den USB-C Anschluss vergrößert,
    diese erschien mir ein bisschen zu klein.
2023-04-21 Bildgröße verkleinert
    Bildgröße verkleinert um Speichplatz zu sparen
2023-04-21 Belegungsplan korrigiert
    Hatte falsche Pinangaben für die 10 Tasten gemacht.
2023-04-26 Alles aktualisiert
2023-04-26 Pinbelegung geändert
2023-05-01 Aktuelle Version mit 10 Buttons
2023-05-01 Bilder Aktualisiert
2023-05-01 Bildgröße geändert
2023-05-01 Beschreibung geändert
2023-05-01 Beschreibung teilweise schon geändert
2023-05-02 Beschreibung angepasst
2023-05-02 Beschreibung aktualisiert
2023-05-02 Beschreibung erweitert
2023-05-02 Test geändert
2023-05-02 Bild hinzugefügt
2023-05-02 Bildverlinkung geändert
2023-05-02 Text geändert
2023-05-02 Fehler im Text beseitigt
2023-05-02 Doppelte Bilder entfernt
2023-05-02 Bild geändert
2023-05-02 Bilder transparent gemacht
2023-05-03 Bilder geändert
2023-05-03 Bildgröße reduziert
2023-05-03 Readme in English übersetzt
2023-05-03 Deutsche Übersetzung hinzugefügt
2023-05-03 Bilder verkleinert
2023-05-03 Bilderlink korrigiert
2023-05-04 Übersetzung erweitert
2023-05-05 Konfigseite in Deutsch Übersetzt
2023-05-08 Knopffunktionen
2023-05-08 Beschreibung bearbeitet
2023-05-08 Alles aktualisiert außer CAD Dateien
2023-05-09 Einige Fehler behoben
2023-05-10 Update neue Version komplett
2023-05-10 Buttonbelegung gespeichert
2023-05-10 Gelenke hinzugefügt
    Habe in das Modell nur Gelenke eingefügt um zu kontrollieren, ob die Bewegung vom Knopf beim Drehen in Ordnung ist. Aber es ist alles OK.
2023-05-11 Systemphoto Erweiterung geändert
2023-05-11 Bilder optimiert
2023-05-11 Text angepasst
2023-05-11 Schaltplan Bild geändert
2023-05-11 Doppeltes Bild entfernt
2023-05-11 Bilde verkleinert
2023-05-11 Bild transparent gemacht
2023-05-14 Optimierungen
2023-05-14 Update cadparams.json
    Die Einstellungen Funktionieren schon besser.
2023-05-15 Dateien für Platine hinzugefügt
2023-05-15 Update README.md
    Beschreibung angepasst
2023-05-15 Konfiguration gesichert
2023-05-17 Update cadparams.json
    Parameter angepasst
2023-05-18 Hallsensor hatte die falsche Bezeichnung
2023-05-19 Schaltplan aktualisiert
    Ist noch nicht ganz fertig um ein Board zu erstellen
2023-05-19 Platinen Erstellung in Arbeit
2023-05-19 Update CADDeck.kicad_pcb
    Platine größer gemacht
2023-05-21 Platine geroutet
    aber noch nicht auf Fehler überprüft
2023-05-21 Platinendaten gelöscht
2023-05-21 Platine aktualisiert
2023-05-21 deadzone geändert
2023-05-22 Platine aktualisiert
    LED Beleuchtung für Tasten
2023-05-23 Platine Fehler beseitigt
2023-05-23 Platine fertig gestellt
2023-05-23 Alle Platinen fertiggestellt
2023-05-24 Broken Link repariert
2023-05-24 Auf Version 0.0.13 aktualisiert
2023-05-26 Config Parameter
    Config für Knopf aktualisiert
2023-05-26 Icon Aktualisiert
2023-05-26 Update index.htm
    Ins deutsche übersetzt
2023-05-28 Parameter angepasst
2023-05-28 Übersetzung korrigiert
2023-05-28 Übersetzung in deutsch.
2023-05-28 Übersetzung vervollständigt.
2023-05-28 html korrigiert
2023-05-28 Übersetzungsfehler bereinigt
2023-05-28 Zeilenumbruch geändert
2023-05-28 Update KiCad.bmp
    Hintergrund geändert
2023-05-29 Langlöcher etwas verlängert
    Beschreibung erweitert
2023-05-29 Update M4_hex_standoff.png
    Bildgröße geändert
2023-05-29 versionnumber = "0.0.16_10Button
2023-05-29 MX_LED_Beleuchtung hinzugefügt
2023-06-01 Bilder und Schaltplan aktualisiert
2023-06-04 Energiesparfunktion aktiviert
2023-06-04 Board Transistor eingefügt
    Für LED Beleuchtung und Leiterbahnen angepasst.
2023-06-05 Symbole für Beleuchtung hinzugefügt
2023-06-05 Platine optimiert
    und Gerberdateien aktualisiert.
2023-06-06 Platinen optimiert
2023-06-07 Platine Optimiert
2023-06-08 Platinenversion
    Dateien angepasst, damit die Platine ins Gehäuse passt.
    Die Schalterkappen habe ich auch etwas verändern müssen, damit die LED's in dem MX-Tastern passen, außerdem habe ich die Tasten außen etwas verkleinert, damit sie besser ins Gehäuse passen.
2023-06-09 Stecker verrückt
    um mehr Platz an den Abstandshaltern zu bekommen.
2023-06-09 Neue Platine in 3D Modell eingefügt
2023-06-09 Bild aktualisiert
2023-06-11 Montage ohne Platine
    falls Montage ohne Schalterplatine
2023-06-11 Update Gerber.zip
    Gerberfile war kaputt
2023-06-11 Massefläche hinzugefügt
    Massefläche hinzugefügt
2023-06-11 Pinzuordnung geändert
2023-06-11 Update Pin Usage.docx
    Pinzuordnung geändert
2023-06-12 Platinenbeschriftung erweitert
2023-06-12 Kleine Korrekturen
2023-06-12 Version 0.0.17_10Button
2023-06-12 Icon hinzugefügt
2023-06-12 Version 0.0.17
2023-06-13 Fehler korrigiert
2023-06-13 Einstellung für Platinenversion hinzugefügt
2023-06-14 Schraubenlänge geändert
    Beschreibung angepasst
2023-06-14 Deutsche Übersetzung
    und Preisliste angehängt
2023-06-14 Beschreibung
    Übersetzungsfehler korrigiert
2023-06-14 Beschreibung
    Bildfehler korrigiert
2023-06-14 Bildverknüpfung geändert
2023-06-14 Create READMEeng.md
    Englische Beschreibung
2023-06-16 Abstand zur Platine verringert.
2023-06-16 Geringfügige Änderung Abstandshalter Platine
2023-06-17 Platine Steckerausrichtung geändert
    Nur der Optik wegen
2023-06-17 Knopf Platine aktualisiert
2023-06-18 Footprints geändert
2023-06-21 Platinenbeschriftung korrigiert
2023-06-21 Platine neu ausgerichtet und kontrolliert
2023-06-21 Bild verkleinert
    Beschreibung geändert
2023-06-21 Link zu englischen Anleitung hinzugefügt
2023-06-21 Rechtschreibfehler korrigiert
2023-06-21 Update READMEeng.md
    Englische Beschreibung erweitert
2023-06-24 Kondensatoren hinzugefügt
2023-06-24 Schaltplan aktualisiert
2023-06-28 NPN durch PNP Transistor getauscht
2023-06-29 LED Ansteuerung
    hatte eine falsche Verbindung am Transistor
2023-06-30 Transistor für LED Ansteuerung geändert
2023-07-05 Transistor geändert
    Bei KiCad war ein fehlerhafter Footprint.
2023-07-09 Habe am Modell nur ein paar Radien hinzugefügt.
    Und die Zentrierhilfe etwas dicker gemacht
2023-07-14 PCG8575 A0-A1 auf GND gelegt
    Muss noch getestet werden, da der PCF nicht funktionierte.
2023-07-15 Bild im Schaltplan aktualisiert
2023-08-27 Magnethalter
    Führungen um 0,1mm verkleinert
2023-11-09 Kleine Optimierungen am Knopf
    Bohrungen vergrößert und Führungen durch Abstandshalter ALU M2,5 x 15 mm ersetzt.
2023-11-10 Geringfügige Änderung
    Position der Magnete geändert, damit es besser zu drucken ist.
2023-11-12 Knob Platine neu erstellt
    Lötpads anstelle eines Pinheaders angebracht, da wenig Platz unter dem Knob ist. Vereinfacht das Löten.
2023-11-22 Stückliste ergänzt
    Und kleine Optimierungen
2023-11-26 Änderung am Deckel
    Der Touchsensor sollte nun einrasten und braucht nicht geklebt zu werden.
    Somit kann dieser zum Schluss eingebaut werden und erleichtert die Montage.
2023-12-07 Software Vers. 1.1.4
2023-12-08 RP2040 Firmware hinzugefügt
2023-12-08 Schreibfehler behoben
2023-12-09 Pin in GPIO geändert
2023-12-29 Knob Platine hatte Fehler
2024-01-22 Gehäuse geteilt
    Damit es auf kleinere Drucker passt
2024-02-05 Neues Gehäuse
    Ist noch nicht fertig.
